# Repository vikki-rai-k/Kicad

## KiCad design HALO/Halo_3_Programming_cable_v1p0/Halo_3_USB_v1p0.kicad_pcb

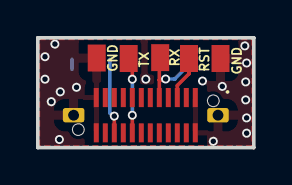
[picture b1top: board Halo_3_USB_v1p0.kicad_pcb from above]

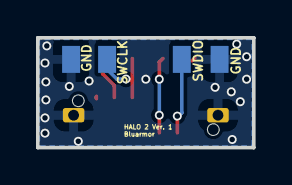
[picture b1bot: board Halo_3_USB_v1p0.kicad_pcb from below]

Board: 2 copper layers, 12.0 x 6.1 mm, 10 parts (4 on the bottom side), 5 nets.

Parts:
J1, J2, J3, J5, J6, J7, J8, J10, J11: Conn_01x01_Pin; Test_Point_1.5mm_SMD_Tiny
J4: Shouhan_TypeC_24_vertical

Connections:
/GND: J1.1, J2.1, J4.A1 (GND_1), J4.A12 (GND_2), J4.B1 (GND_3), J4.B12 (GND_4), J4.MH1, J4.MH2, J8.1, J11.1
/RTL_UART_RX: J3.1, J4.A5 (CC1), J6.1
/RTL_UART_TX: J4.B5 (CC2), J5.1
/ST_SWDIO: J4.B3 (SSTXN2), J7.1
/ST_nRST: J4.A3 (SSTXN1), J10.1

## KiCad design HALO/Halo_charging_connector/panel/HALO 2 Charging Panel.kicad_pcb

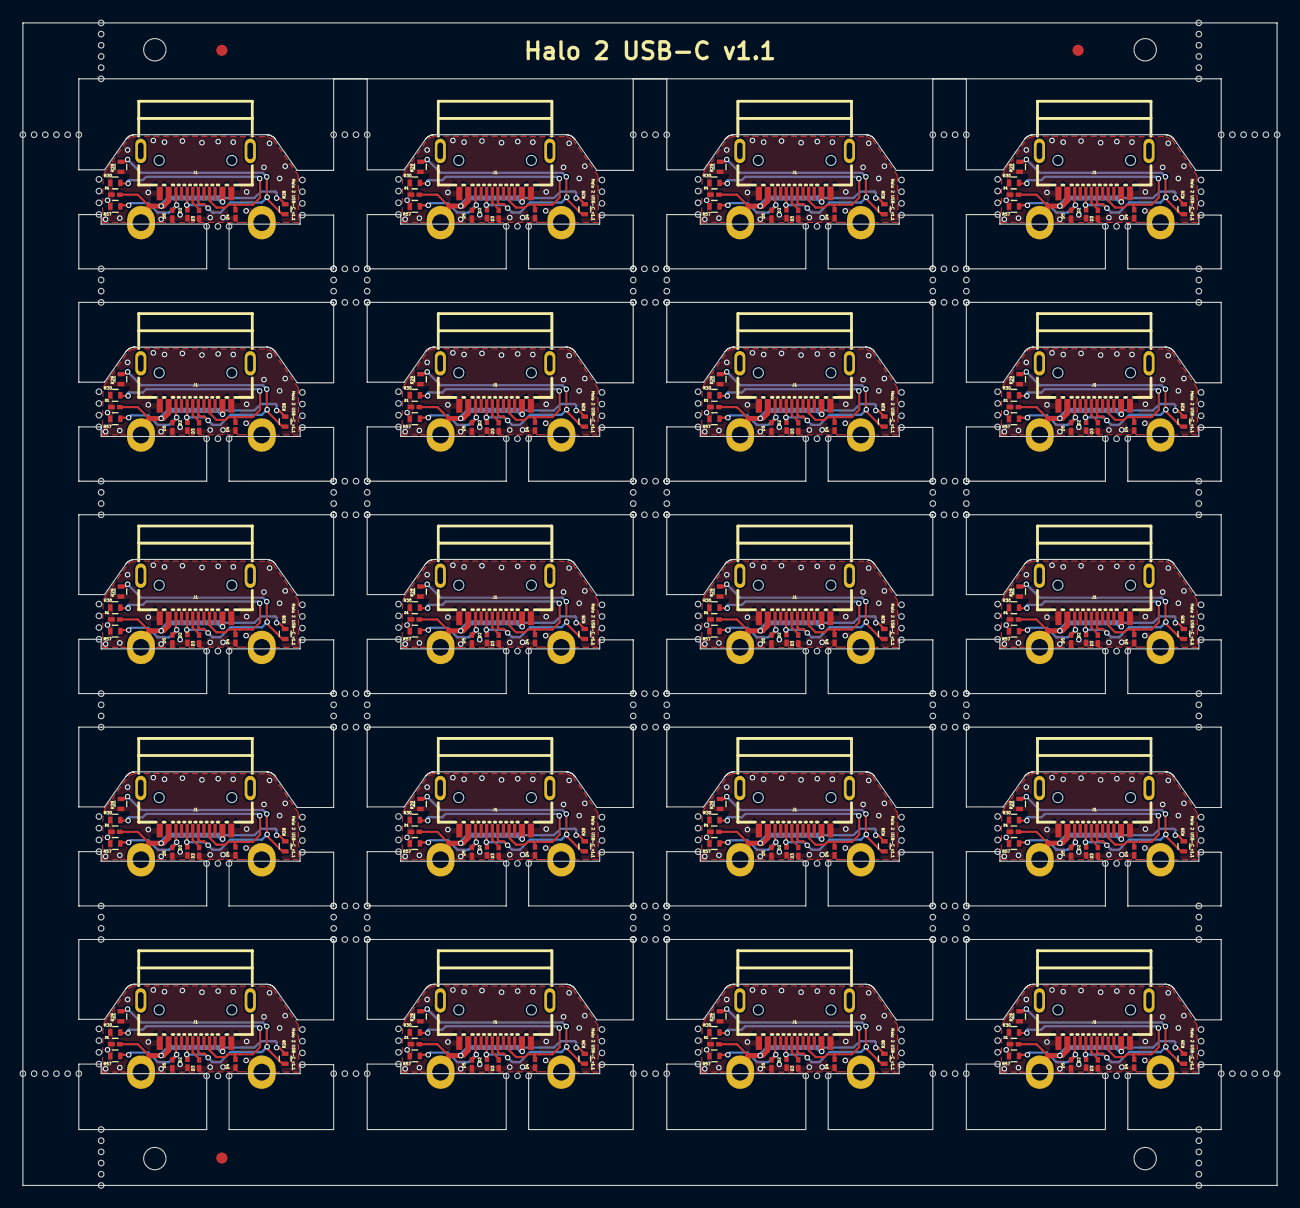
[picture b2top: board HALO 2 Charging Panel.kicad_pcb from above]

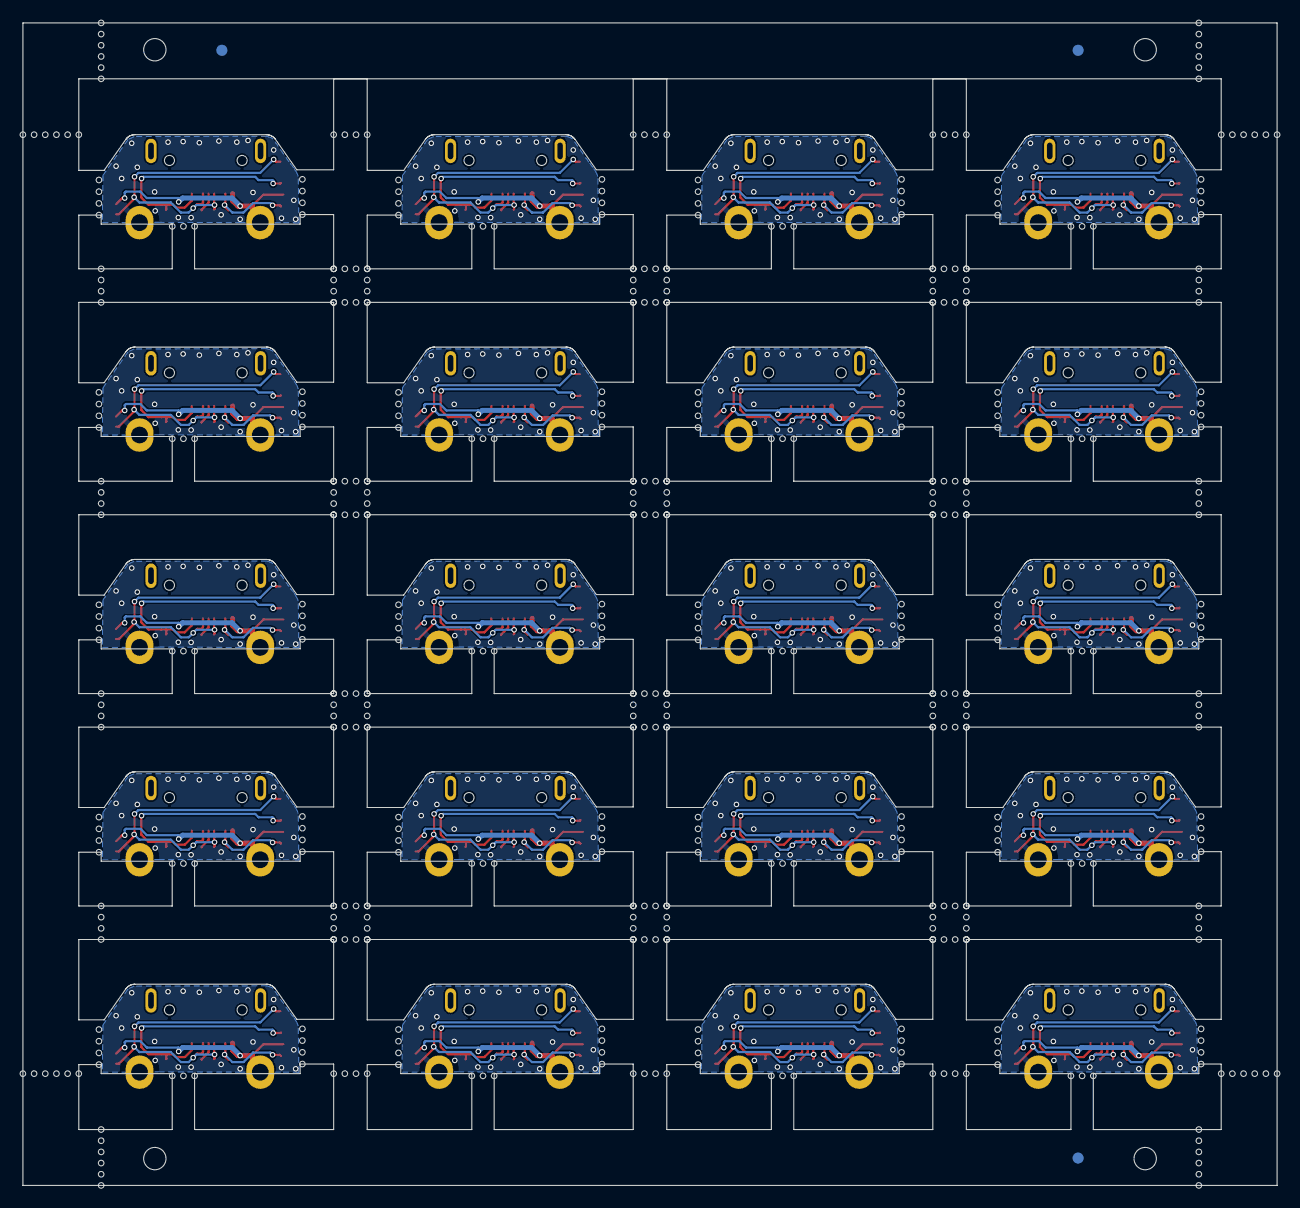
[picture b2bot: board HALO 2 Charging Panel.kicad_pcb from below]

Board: 2 copper layers, 112.2 x 104.0 mm, 766 parts (3 on the bottom side), 120 nets.

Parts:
D1, D1#2, D1#3, D1#4, D1#5, D1#6, D1#7, D1#8, D1#9, D1#10, D1#11, D1#12, D1#13, D1#14, D1#15, D1#16, D1#17, D1#18, D1#19, D1#20, D2, D2#2, D2#3, D2#4, D2#5, D2#6, D2#7, D2#8, D2#9, D2#10, D2#11, D2#12, D2#13, D2#14, D2#15, D2#16, D2#17, D2#18, D2#19, D2#20, D3, D3#2, D3#3, D3#4, D3#5, D3#6, D3#7, D3#8, D3#9, D3#10, D3#11, D3#12, D3#13, D3#14, D3#15, D3#16, D3#17, D3#18, D3#19, D3#20, D4, D4#2, D4#3, D4#4, D4#5, D4#6, D4#7, D4#8, D4#9, D4#10, D4#11, D4#12, D4#13, D4#14, D4#15, D4#16, D4#17, D4#18, D4#19, D4#20, D5, D5#2, D5#3, D5#4, D5#5, D5#6, D5#7, D5#8, D5#9, D5#10, D5#11, D5#12, D5#13, D5#14, D5#15, D5#16, D5#17, D5#18, D5#19, D5#20: ESD5451X2TR
J1, J1#2, J1#3, J1#4, J1#5, J1#6, J1#7, J1#8, J1#9, J1#10, J1#11, J1#12, J1#13, J1#14, J1#15, J1#16, J1#17, J1#18, J1#19, J1#20: TYPE-C 16PFS 2JCB1.6-H7.45 IPX8; USB-SMD_TYPE-C-16PFS-2J-H7.45-IPX8
KiKit_FID_B_1, KiKit_FID_B_2, KiKit_FID_B_3: Fiducial
KiKit_FID_T_1, KiKit_FID_T_2, KiKit_FID_T_3: Fiducial
KiKit_MB_1_1, KiKit_MB_1_2, KiKit_MB_1_3, KiKit_MB_2_1, KiKit_MB_2_2, KiKit_MB_2_3, KiKit_MB_2_4, KiKit_MB_3_2, KiKit_MB_3_3, KiKit_MB_3_4, KiKit_MB_3_5, KiKit_MB_4_1, KiKit_MB_4_2, KiKit_MB_4_3, KiKit_MB_5_1, KiKit_MB_5_2, KiKit_MB_5_3, KiKit_MB_5_4, KiKit_MB_6_2, KiKit_MB_6_3, KiKit_MB_6_4, KiKit_MB_6_5, KiKit_MB_7_1, KiKit_MB_7_2, KiKit_MB_7_3, KiKit_MB_8_1, KiKit_MB_8_2, KiKit_MB_8_3, KiKit_MB_8_4, KiKit_MB_9_2, KiKit_MB_9_3, KiKit_MB_9_4, KiKit_MB_9_5, KiKit_MB_10_1, KiKit_MB_10_2, KiKit_MB_10_3, KiKit_MB_11_1, KiKit_MB_11_2, KiKit_MB_11_3, KiKit_MB_11_4, KiKit_MB_12_2, KiKit_MB_12_3, KiKit_MB_12_4, KiKit_MB_12_5, KiKit_MB_13_1, KiKit_MB_13_2, KiKit_MB_13_3, KiKit_MB_14_1, KiKit_MB_14_2, KiKit_MB_14_3, KiKit_MB_14_4, KiKit_MB_15_2, KiKit_MB_15_3, KiKit_MB_15_4, KiKit_MB_15_5, KiKit_MB_16_1, KiKit_MB_16_2, KiKit_MB_16_3, KiKit_MB_17_1, KiKit_MB_17_2, KiKit_MB_17_3, KiKit_MB_17_4, KiKit_MB_18_2, KiKit_MB_18_3, KiKit_MB_18_4, KiKit_MB_18_5, KiKit_MB_19_1, KiKit_MB_19_2, KiKit_MB_19_3, KiKit_MB_20_1, KiKit_MB_20_2, KiKit_MB_20_3, KiKit_MB_20_4, KiKit_MB_21_2, KiKit_MB_21_3, KiKit_MB_21_4, KiKit_MB_21_5, KiKit_MB_22_1, KiKit_MB_22_2, KiKit_MB_22_3, KiKit_MB_23_1, KiKit_MB_23_2, KiKit_MB_23_3, KiKit_MB_23_4, KiKit_MB_24_2, KiKit_MB_24_3, KiKit_MB_24_4, KiKit_MB_24_5, KiKit_MB_25_1, KiKit_MB_25_2, KiKit_MB_25_3, KiKit_MB_26_1, KiKit_MB_26_2, KiKit_MB_26_3, KiKit_MB_26_4, KiKit_MB_27_2, KiKit_MB_27_3, KiKit_MB_27_4, KiKit_MB_27_5, KiKit_MB_28_1, KiKit_MB_28_2, KiKit_MB_28_3, KiKit_MB_29_1, KiKit_MB_29_2, KiKit_MB_29_3, KiKit_MB_29_4, KiKit_MB_30_2, KiKit_MB_30_3, KiKit_MB_30_4, KiKit_MB_30_5, KiKit_MB_31_1, KiKit_MB_31_2, KiKit_MB_31_3, KiKit_MB_32_1, KiKit_MB_32_2, KiKit_MB_32_3, KiKit_MB_32_4, KiKit_MB_33_2, KiKit_MB_33_3, KiKit_MB_33_4, KiKit_MB_33_5, KiKit_MB_34_1, KiKit_MB_34_2, KiKit_MB_34_3, KiKit_MB_35_1, KiKit_MB_35_2, KiKit_MB_35_3, KiKit_MB_35_4, KiKit_MB_36_2, KiKit_MB_36_3, KiKit_MB_36_4, KiKit_MB_36_5, KiKit_MB_37_1, KiKit_MB_37_2, KiKit_MB_37_3, KiKit_MB_38_1, KiKit_MB_38_2, KiKit_MB_38_3, KiKit_MB_38_4, KiKit_MB_39_2, KiKit_MB_39_3, KiKit_MB_39_4, KiKit_MB_39_5, KiKit_MB_40_1, KiKit_MB_40_2, KiKit_MB_40_3, KiKit_MB_41_1, KiKit_MB_41_2, KiKit_MB_41_3, KiKit_MB_41_4, KiKit_MB_42_2, KiKit_MB_42_3, KiKit_MB_42_4, KiKit_MB_42_5, KiKit_MB_43_1, KiKit_MB_43_2, KiKit_MB_43_3, KiKit_MB_44_1, KiKit_MB_44_2, KiKit_MB_44_3, KiKit_MB_44_4, KiKit_MB_45_2, KiKit_MB_45_3, KiKit_MB_45_4, KiKit_MB_45_5, KiKit_MB_46_1, KiKit_MB_46_2, KiKit_MB_46_3, KiKit_MB_47_1, KiKit_MB_47_2, KiKit_MB_47_3, KiKit_MB_47_4, KiKit_MB_48_2, KiKit_MB_48_3, KiKit_MB_48_4, KiKit_MB_48_5, KiKit_MB_49_1, KiKit_MB_49_2, KiKit_MB_49_3, KiKit_MB_50_1, KiKit_MB_50_2, KiKit_MB_50_3, KiKit_MB_50_4, KiKit_MB_51_2, KiKit_MB_51_3, KiKit_MB_51_4, KiKit_MB_51_5, KiKit_MB_52_1, KiKit_MB_52_2, KiKit_MB_52_3, KiKit_MB_53_1, KiKit_MB_53_2, KiKit_MB_53_3, KiKit_MB_53_4, KiKit_MB_54_2, KiKit_MB_54_3, KiKit_MB_54_4, KiKit_MB_54_5, KiKit_MB_55_1, KiKit_MB_55_2, KiKit_MB_55_3, KiKit_MB_56_1, KiKit_MB_56_2, KiKit_MB_56_3, KiKit_MB_56_4, KiKit_MB_57_2, KiKit_MB_57_3, KiKit_MB_57_4, KiKit_MB_57_5, KiKit_MB_58_1, KiKit_MB_58_2, KiKit_MB_58_3, KiKit_MB_59_1, KiKit_MB_59_2, KiKit_MB_59_3, KiKit_MB_59_4, KiKit_MB_60_2, KiKit_MB_60_3, KiKit_MB_60_4, KiKit_MB_60_5, KiKit_MB_61_1, KiKit_MB_61_2, KiKit_MB_61_3, KiKit_MB_61_4, KiKit_MB_62_1, KiKit_MB_62_2, KiKit_MB_62_3, KiKit_MB_62_4, KiKit_MB_63_1, KiKit_MB_63_2, KiKit_MB_63_3, KiKit_MB_63_4, KiKit_MB_64_1, KiKit_MB_64_2, KiKit_MB_64_3, KiKit_MB_64_4, KiKit_MB_65_1, KiKit_MB_65_2, KiKit_MB_65_3, KiKit_MB_65_4, KiKit_MB_66_1, KiKit_MB_66_2, KiKit_MB_66_3, KiKit_MB_66_4, KiKit_MB_67_1, KiKit_MB_67_2, KiKit_MB_67_3, KiKit_MB_67_4, KiKit_MB_68_1, KiKit_MB_68_2, KiKit_MB_68_3, KiKit_MB_68_4, KiKit_MB_69_1, KiKit_MB_69_2, KiKit_MB_69_3, KiKit_MB_69_4, KiKit_MB_70_1, KiKit_MB_70_2, KiKit_MB_70_3, KiKit_MB_70_4, KiKit_MB_71_1, KiKit_MB_71_2, KiKit_MB_71_3, KiKit_MB_71_4, KiKit_MB_72_1, KiKit_MB_72_2, KiKit_MB_72_3, KiKit_MB_72_4, KiKit_MB_73_1, KiKit_MB_73_2, KiKit_MB_73_3, KiKit_MB_73_4, KiKit_MB_74_1, KiKit_MB_74_2, KiKit_MB_74_3, KiKit_MB_74_4, KiKit_MB_75_1, KiKit_MB_75_2, KiKit_MB_75_3, KiKit_MB_75_4, KiKit_MB_76_1, KiKit_MB_76_2, KiKit_MB_76_3, KiKit_MB_76_4, KiKit_MB_77_1, KiKit_MB_77_2, KiKit_MB_77_3, KiKit_MB_77_4, KiKit_MB_78_1, KiKit_MB_78_2, KiKit_MB_78_3, KiKit_MB_78_4, KiKit_MB_79_1, KiKit_MB_79_2, KiKit_MB_79_3, KiKit_MB_79_4, KiKit_MB_80_1, KiKit_MB_80_2, KiKit_MB_80_3, KiKit_MB_80_4, KiKit_MB_81_1, KiKit_MB_81_2, KiKit_MB_81_3, KiKit_MB_81_4, KiKit_MB_82_1, KiKit_MB_82_2, KiKit_MB_82_3, KiKit_MB_82_4, KiKit_MB_83_1, KiKit_MB_83_2, KiKit_MB_83_3, KiKit_MB_83_4, KiKit_MB_84_1, KiKit_MB_84_2, KiKit_MB_84_3, KiKit_MB_84_4, KiKit_MB_85_1, KiKit_MB_85_2, KiKit_MB_85_3, KiKit_MB_85_4, KiKit_MB_86_1, KiKit_MB_86_2, KiKit_MB_86_3, KiKit_MB_86_4, KiKit_MB_87_1, KiKit_MB_87_2, KiKit_MB_87_3, KiKit_MB_87_4, KiKit_MB_88_1, KiKit_MB_88_2, KiKit_MB_88_3, KiKit_MB_88_4, KiKit_MB_89_1, KiKit_MB_89_2, KiKit_MB_89_3, KiKit_MB_89_4, KiKit_MB_90_1, KiKit_MB_90_2, KiKit_MB_90_3, KiKit_MB_90_4, KiKit_MB_91_1, KiKit_MB_91_2, KiKit_MB_91_3, KiKit_MB_91_4, KiKit_MB_92_1, KiKit_MB_92_2, KiKit_MB_92_3, KiKit_MB_92_4, KiKit_MB_93_1, KiKit_MB_93_2, KiKit_MB_93_3, KiKit_MB_93_4, KiKit_MB_94_1, KiKit_MB_94_2, KiKit_MB_94_3, KiKit_MB_94_4, KiKit_MB_95_1, KiKit_MB_95_2, KiKit_MB_95_3, KiKit_MB_95_4, KiKit_MB_96_1, KiKit_MB_96_2, KiKit_MB_96_3, KiKit_MB_96_4, KiKit_MB_97_1, KiKit_MB_97_2, KiKit_MB_97_3, KiKit_MB_97_4, KiKit_MB_98_1, KiKit_MB_98_2, KiKit_MB_98_3, KiKit_MB_98_4, KiKit_MB_99_1, KiKit_MB_99_2, KiKit_MB_99_3, KiKit_MB_99_4, KiKit_MB_100_1, KiKit_MB_100_2, KiKit_MB_100_3, KiKit_MB_100_4, KiKit_MB_101_1, KiKit_MB_101_2, KiKit_MB_101_3, KiKit_MB_101_4, KiKit_MB_102_1, KiKit_MB_102_2, KiKit_MB_102_3, KiKit_MB_102_4, KiKit_MB_103_1, KiKit_MB_103_2, KiKit_MB_103_3, KiKit_MB_103_4, KiKit_MB_104_1, KiKit_MB_104_2, KiKit_MB_104_3, KiKit_MB_104_4, KiKit_MB_105_1, KiKit_MB_105_2, KiKit_MB_105_3, KiKit_MB_105_4, KiKit_MB_106_1, KiKit_MB_106_2, KiKit_MB_106_3, KiKit_MB_106_4, KiKit_MB_107_1, KiKit_MB_107_2, KiKit_MB_107_3, KiKit_MB_107_4, KiKit_MB_108_1, KiKit_MB_108_2, KiKit_MB_108_3, KiKit_MB_108_4, KiKit_MB_109_1, KiKit_MB_109_2, KiKit_MB_109_3, KiKit_MB_109_4, KiKit_MB_110_1, KiKit_MB_110_2, KiKit_MB_110_3, KiKit_MB_110_4, KiKit_MB_111_1, KiKit_MB_111_2, KiKit_MB_111_3, KiKit_MB_111_4, KiKit_MB_112_1, KiKit_MB_112_2, KiKit_MB_112_3, KiKit_MB_112_4, KiKit_MB_113_1, KiKit_MB_113_2, KiKit_MB_113_3, KiKit_MB_113_4, KiKit_MB_114_1, KiKit_MB_114_2, KiKit_MB_114_3, KiKit_MB_114_4, KiKit_MB_115_1, KiKit_MB_115_2, KiKit_MB_115_3, KiKit_MB_115_4, KiKit_MB_116_1, KiKit_MB_116_2, KiKit_MB_116_3, KiKit_MB_116_4, KiKit_MB_117_1, KiKit_MB_117_2, KiKit_MB_117_3, KiKit_MB_117_4, KiKit_MB_118_1, KiKit_MB_118_2, KiKit_MB_118_3, KiKit_MB_118_4, KiKit_MB_119_1, KiKit_MB_119_2, KiKit_MB_119_3, KiKit_MB_119_4, KiKit_MB_120_1, KiKit_MB_120_2, KiKit_MB_120_3, KiKit_MB_120_4, KiKit_MB_121_1, KiKit_MB_121_2, KiKit_MB_121_3, KiKit_MB_121_4, KiKit_MB_122_1, KiKit_MB_122_2, KiKit_MB_122_3, KiKit_MB_122_4, KiKit_MB_123_1, KiKit_MB_123_2, KiKit_MB_123_3, KiKit_MB_123_4, KiKit_MB_123_5, KiKit_MB_123_6, KiKit_MB_124_1, KiKit_MB_124_2, KiKit_MB_124_3, KiKit_MB_124_4, KiKit_MB_124_5, KiKit_MB_124_6, KiKit_MB_125_1, KiKit_MB_125_2, KiKit_MB_125_3, KiKit_MB_125_4, KiKit_MB_125_5, KiKit_MB_125_6, KiKit_MB_126_1, KiKit_MB_126_2, KiKit_MB_126_3, KiKit_MB_126_4, KiKit_MB_126_5, KiKit_MB_126_6, KiKit_MB_127_1, KiKit_MB_127_2, KiKit_MB_127_3, KiKit_MB_127_4, KiKit_MB_127_5, KiKit_MB_127_6, KiKit_MB_128_1, KiKit_MB_128_2, KiKit_MB_128_3, KiKit_MB_128_4, KiKit_MB_128_5, KiKit_MB_128_6, KiKit_MB_129_1, KiKit_MB_129_2, KiKit_MB_129_3, KiKit_MB_129_4, KiKit_MB_129_5, KiKit_MB_129_6, KiKit_MB_130_1, KiKit_MB_130_2, KiKit_MB_130_3, KiKit_MB_130_4, KiKit_MB_130_5, KiKit_MB_130_6: NPTH
KiKit_TO_1, KiKit_TO_2, KiKit_TO_3, KiKit_TO_4: NPTH
R28, R28#2, R28#3, R28#4, R28#5, R28#6, R28#7, R28#8, R28#9, R28#10, R28#11, R28#12, R28#13, R28#14, R28#15, R28#16, R28#17, R28#18, R28#19, R28#20: 60.4K; R_0402
R29, R29#2, R29#3, R29#4, R29#5, R29#6, R29#7, R29#8, R29#9, R29#10, R29#11, R29#12, R29#13, R29#14, R29#15, R29#16, R29#17, R29#18, R29#19, R29#20: 10K; R_0402
R30, R30#2, R30#3, R30#4, R30#5, R30#6, R30#7, R30#8, R30#9, R30#10, R30#11, R30#12, R30#13, R30#14, R30#15, R30#16, R30#17, R30#18, R30#19, R30#20, R57, R57#2, R57#3, R57#4, R57#5, R57#6, R57#7, R57#8, R57#9, R57#10, R57#11, R57#12, R57#13, R57#14, R57#15, R57#16, R57#17, R57#18, R57#19, R57#20: 5.1K; R_0402
U1, U1#2, U1#3, U1#4, U1#5, U1#6, U1#7, U1#8, U1#9, U1#10, U1#11, U1#12, U1#13, U1#14, U1#15, U1#16, U1#17, U1#18, U1#19, U1#20, U2, U2#2, U2#3, U2#4, U2#5, U2#6, U2#7, U2#8, U2#9, U2#10, U2#11, U2#12, U2#13, U2#14, U2#15, U2#16, U2#17, U2#18, U2#19, U2#20: -; Halo_2_USBC_Charging_PCB_Castellated_holes

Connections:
Board_0-/CC1: D4#6.2 (A2), J1#15.A5 (CC1), R30#20.1
Board_0-/CC2: D5#17.2 (A2), J1#15.B5 (CC2), R57#17.1
Board_0-/DN: D3#16.2 (A2), J1#15.A7 (DA_N)
Board_0-/DP: D2#15.2 (A2), J1#15.A6 (DA_P), J1#15.B6 (DB_P), R28#20.2, R29#2.1
Board_0-/GND: D1#12.1 (A1), D2#15.1 (A1), D3#16.1 (A1), D4#6.1 (A1), D5#17.1 (A1), J1#15.B1A12 (GNDB), J1#15.B12A1 (GNDA), R29#2.2, R30#20.2, R57#17.2, U2#20.1
Board_0-/VUSB: D1#12.2 (A2), J1#15.A4B9 (VBUS_A), J1#15.A9B4 (VBUS_B), R28#20.1, U1#11.1
Board_1-/CC1: D4#20.2 (A2), J1#4.A5 (CC1), R30#15.1
Board_1-/CC2: D5#3.2 (A2), J1#4.B5 (CC2), R57#11.1
Board_1-/DN: D3#6.2 (A2), J1#4.A7 (DA_N)
Board_1-/DP: D2#12.2 (A2), J1#4.A6 (DA_P), J1#4.B6 (DB_P), R28#19.2, R29#7.1
Board_1-/GND: D1#9.1 (A1), D2#12.1 (A1), D3#6.1 (A1), D4#20.1 (A1), D5#3.1 (A1), J1#4.B1A12 (GNDB), J1#4.B12A1 (GNDA), R29#7.2, R30#15.2, R57#11.2, U2#4.1
Board_1-/VUSB: D1#9.2 (A2), J1#4.A4B9 (VBUS_A), J1#4.A9B4 (VBUS_B), R28#19.1, U1#13.1
Board_2-/CC1: D4#5.2 (A2), J1#3.A5 (CC1), R30#10.1
Board_2-/CC2: D5#11.2 (A2), J1#3.B5 (CC2), R57#13.1
Board_2-/DN: D3#2.2 (A2), J1#3.A7 (DA_N)
Board_2-/DP: D2#20.2 (A2), J1#3.A6 (DA_P), J1#3.B6 (DB_P), R28#17.2, R29#8.1
Board_2-/GND: D1#11.1 (A1), D2#20.1 (A1), D3#2.1 (A1), D4#5.1 (A1), D5#11.1 (A1), J1#3.B1A12 (GNDB), J1#3.B12A1 (GNDA), R29#8.2, R30#10.2, R57#13.2, U2#17.1
Board_2-/VUSB: D1#11.2 (A2), J1#3.A4B9 (VBUS_A), J1#3.A9B4 (VBUS_B), R28#17.1, U1#5.1
Board_3-/CC1: D4#16.2 (A2), J1#16.A5 (CC1), R30#14.1
Board_3-/CC2: D5#18.2 (A2), J1#16.B5 (CC2), R57#5.1
Board_3-/DN: D3#5.2 (A2), J1#16.A7 (DA_N)
Board_3-/DP: D2#14.2 (A2), J1#16.A6 (DA_P), J1#16.B6 (DB_P), R28#16.2, R29#19.1
Board_3-/GND: D1#5.1 (A1), D2#14.1 (A1), D3#5.1 (A1), D4#16.1 (A1), D5#18.1 (A1), J1#16.B1A12 (GNDB), J1#16.B12A1 (GNDA), R29#19.2, R30#14.2, R57#5.2, U2#10.1
Board_3-/VUSB: D1#5.2 (A2), J1#16.A4B9 (VBUS_A), J1#16.A9B4 (VBUS_B), R28#16.1, U1#6.1
Board_4-/CC1: D4#11.2 (A2), J1#19.A5 (CC1), R30#2.1
Board_4-/CC2: D5#15.2 (A2), J1#19.B5 (CC2), R57#18.1
Board_4-/DN: D3#20.2 (A2), J1#19.A7 (DA_N)
Board_4-/DP: D2#5.2 (A2), J1#19.A6 (DA_P), J1#19.B6 (DB_P), R28#4.2, R29#11.1
Board_4-/GND: D1#2.1 (A1), D2#5.1 (A1), D3#20.1 (A1), D4#11.1 (A1), D5#15.1 (A1), J1#19.B1A12 (GNDB), J1#19.B12A1 (GNDA), R29#11.2, R30#2.2, R57#18.2, U2#19.1
Board_4-/VUSB: D1#2.2 (A2), J1#19.A4B9 (VBUS_A), J1#19.A9B4 (VBUS_B), R28#4.1, U1#8.1
Board_5-/CC1: D4#15.2 (A2), J1#2.A5 (CC1), R30#16.1
Board_5-/CC2: D5#14.2 (A2), J1#2.B5 (CC2), R57#8.1
Board_5-/DN: D3#8.2 (A2), J1#2.A7 (DA_N)
Board_5-/DP: D2#18.2 (A2), J1#2.A6 (DA_P), J1#2.B6 (DB_P), R28#10.2, R29#3.1
Board_5-/GND: D1#16.1 (A1), D2#18.1 (A1), D3#8.1 (A1), D4#15.1 (A1), D5#14.1 (A1), J1#2.B1A12 (GNDB), J1#2.B12A1 (GNDA), R29#3.2, R30#16.2, R57#8.2, U2#14.1
Board_5-/VUSB: D1#16.2 (A2), J1#2.A4B9 (VBUS_A), J1#2.A9B4 (VBUS_B), R28#10.1, U1#18.1
Board_6-/CC1: D4#9.2 (A2), J1#9.A5 (CC1), R30#19.1
Board_6-/CC2: D5#19.2 (A2), J1#9.B5 (CC2), R57#10.1
Board_6-/DN: D3#10.2 (A2), J1#9.A7 (DA_N)
Board_6-/DP: D2#11.2 (A2), J1#9.A6 (DA_P), J1#9.B6 (DB_P), R28#6.2, R29#15.1
Board_6-/GND: D1#20.1 (A1), D2#11.1 (A1), D3#10.1 (A1), D4#9.1 (A1), D5#19.1 (A1), J1#9.B1A12 (GNDB), J1#9.B12A1 (GNDA), R29#15.2, R30#19.2, R57#10.2, U2#8.1
Board_6-/VUSB: D1#20.2 (A2), J1#9.A4B9 (VBUS_A), J1#9.A9B4 (VBUS_B), R28#6.1, U1#4.1
Board_7-/CC1: D4#2.2 (A2), J1.A5 (CC1), R30#3.1
Board_7-/CC2: D5#5.2 (A2), J1.B5 (CC2), R57#19.1
Board_7-/DN: D3#11.2 (A2), J1.A7 (DA_N)
Board_7-/DP: D2#4.2 (A2), J1.A6 (DA_P), J1.B6 (DB_P), R28#11.2, R29#20.1
Board_7-/GND: D1#19.1 (A1), D2#4.1 (A1), D3#11.1 (A1), D4#2.1 (A1), D5#5.1 (A1), J1.B1A12 (GNDB), J1.B12A1 (GNDA), R29#20.2, R30#3.2, R57#19.2, U2#16.1
Board_7-/VUSB: D1#19.2 (A2), J1.A4B9 (VBUS_A), J1.A9B4 (VBUS_B), R28#11.1, U1#19.1
Board_8-/CC1: D4#12.2 (A2), J1#20.A5 (CC1), R30#4.1
Board_8-/CC2: D5#7.2 (A2), J1#20.B5 (CC2), R57#20.1
Board_8-/DN: D3#12.2 (A2), J1#20.A7 (DA_N)
Board_8-/DP: D2.2 (A2), J1#20.A6 (DA_P), J1#20.B6 (DB_P), R28#9.2, R29#12.1
Board_8-/GND: D1.1 (A1), D2.1 (A1), D3#12.1 (A1), D4#12.1 (A1), D5#7.1 (A1), J1#20.B1A12 (GNDB), J1#20.B12A1 (GNDA), R29#12.2, R30#4.2, R57#20.2, U2#6.1
Board_8-/VUSB: D1.2 (A2), J1#20.A4B9 (VBUS_A), J1#20.A9B4 (VBUS_B), R28#9.1, U1#16.1
Board_9-/CC1: D4#4.2 (A2), J1#8.A5 (CC1), R30#17.1
Board_9-/CC2: D5#20.2 (A2), J1#8.B5 (CC2), R57#6.1
Board_9-/DN: D3#19.2 (A2), J1#8.A7 (DA_N)
Board_9-/DP: D2#7.2 (A2), J1#8.A6 (DA_P), J1#8.B6 (DB_P), R28#14.2, R29#16.1
Board_9-/GND: D1#8.1 (A1), D2#7.1 (A1), D3#19.1 (A1), D4#4.1 (A1), D5#20.1 (A1), J1#8.B1A12 (GNDB), J1#8.B12A1 (GNDA), R29#16.2, R30#17.2, R57#6.2, U2.1
Board_9-/VUSB: D1#8.2 (A2), J1#8.A4B9 (VBUS_A), J1#8.A9B4 (VBUS_B), R28#14.1, U1#7.1
Board_10-/CC1: D4#13.2 (A2), J1#10.A5 (CC1), R30#6.1
Board_10-/CC2: D5.2 (A2), J1#10.B5 (CC2), R57#7.1
Board_10-/DN: D3#13.2 (A2), J1#10.A7 (DA_N)
Board_10-/DP: D2#6.2 (A2), J1#10.A6 (DA_P), J1#10.B6 (DB_P), R28#13.2, R29#6.1
Board_10-/GND: D1#17.1 (A1), D2#6.1 (A1), D3#13.1 (A1), D4#13.1 (A1), D5.1 (A1), J1#10.B1A12 (GNDB), J1#10.B12A1 (GNDA), R29#6.2, R30#6.2, R57#7.2, U2#11.1
Board_10-/VUSB: D1#17.2 (A2), J1#10.A4B9 (VBUS_A), J1#10.A9B4 (VBUS_B), R28#13.1, U1#20.1
Board_11-/CC1: D4#14.2 (A2), J1#13.A5 (CC1), R30#9.1
Board_11-/CC2: D5#6.2 (A2), J1#13.B5 (CC2), R57#3.1
Board_11-/DN: D3#14.2 (A2), J1#13.A7 (DA_N)
Board_11-/DP: D2#17.2 (A2), J1#13.A6 (DA_P), J1#13.B6 (DB_P), R28#7.2, R29.1
Board_11-/GND: D1#6.1 (A1), D2#17.1 (A1), D3#14.1 (A1), D4#14.1 (A1), D5#6.1 (A1), J1#13.B1A12 (GNDB), J1#13.B12A1 (GNDA), R29.2, R30#9.2, R57#3.2, U2#3.1
Board_11-/VUSB: D1#6.2 (A2), J1#13.A4B9 (VBUS_A), J1#13.A9B4 (VBUS_B), R28#7.1, U1#10.1
Board_12-/CC1: D4#8.2 (A2), J1#7.A5 (CC1), R30#12.1
Board_12-/CC2: D5#13.2 (A2), J1#7.B5 (CC2), R57#4.1
Board_12-/DN: D3.2 (A2), J1#7.A7 (DA_N)
Board_12-/DP: D2#2.2 (A2), J1#7.A6 (DA_P), J1#7.B6 (DB_P), R28#3.2, R29#18.1
Board_12-/GND: D1#13.1 (A1), D2#2.1 (A1), D3.1 (A1), D4#8.1 (A1), D5#13.1 (A1), J1#7.B1A12 (GNDB), J1#7.B12A1 (GNDA), R29#18.2, R30#12.2, R57#4.2, U2#18.1
Board_12-/VUSB: D1#13.2 (A2), J1#7.A4B9 (VBUS_A), J1#7.A9B4 (VBUS_B), R28#3.1, U1#15.1
Board_13-/CC1: D4#10.2 (A2), J1#14.A5 (CC1), R30#8.1
Board_13-/CC2: D5#8.2 (A2), J1#14.B5 (CC2), R57#15.1
Board_13-/DN: D3#4.2 (A2), J1#14.A7 (DA_N)
Board_13-/DP: D2#13.2 (A2), J1#14.A6 (DA_P), J1#14.B6 (DB_P), R28#12.2, R29#17.1
Board_13-/GND: D1#3.1 (A1), D2#13.1 (A1), D3#4.1 (A1), D4#10.1 (A1), D5#8.1 (A1), J1#14.B1A12 (GNDB), J1#14.B12A1 (GNDA), R29#17.2, R30#8.2, R57#15.2, U2#2.1
Board_13-/VUSB: D1#3.2 (A2), J1#14.A4B9 (VBUS_A), J1#14.A9B4 (VBUS_B), R28#12.1, U1#9.1
Board_14-/CC1: D4#19.2 (A2), J1#11.A5 (CC1), R30#18.1
Board_14-/CC2: D5#4.2 (A2), J1#11.B5 (CC2), R57#12.1
Board_14-/DN: D3#7.2 (A2), J1#11.A7 (DA_N)
Board_14-/DP: D2#19.2 (A2), J1#11.A6 (DA_P), J1#11.B6 (DB_P), R28.2, R29#4.1
Board_14-/GND: D1#4.1 (A1), D2#19.1 (A1), D3#7.1 (A1), D4#19.1 (A1), D5#4.1 (A1), J1#11.B1A12 (GNDB), J1#11.B12A1 (GNDA), R29#4.2, R30#18.2, R57#12.2, U2#7.1
Board_14-/VUSB: D1#4.2 (A2), J1#11.A4B9 (VBUS_A), J1#11.A9B4 (VBUS_B), R28.1, U1#2.1
Board_15-/CC1: D4#7.2 (A2), J1#12.A5 (CC1), R30.1
Board_15-/CC2: D5#12.2 (A2), J1#12.B5 (CC2), R57#9.1
Board_15-/DN: D3#9.2 (A2), J1#12.A7 (DA_N)
Board_15-/DP: D2#9.2 (A2), J1#12.A6 (DA_P), J1#12.B6 (DB_P), R28#5.2, R29#5.1
Board_15-/GND: D1#15.1 (A1), D2#9.1 (A1), D3#9.1 (A1), D4#7.1 (A1), D5#12.1 (A1), J1#12.B1A12 (GNDB), J1#12.B12A1 (GNDA), R29#5.2, R30.2, R57#9.2, U2#13.1
Board_15-/VUSB: D1#15.2 (A2), J1#12.A4B9 (VBUS_A), J1#12.A9B4 (VBUS_B), R28#5.1, U1#12.1
Board_16-/CC1: D4#18.2 (A2), J1#17.A5 (CC1), R30#5.1
Board_16-/CC2: D5#2.2 (A2), J1#17.B5 (CC2), R57.1
Board_16-/DN: D3#3.2 (A2), J1#17.A7 (DA_N)
Board_16-/DP: D2#16.2 (A2), J1#17.A6 (DA_P), J1#17.B6 (DB_P), R28#15.2, R29#14.1
Board_16-/GND: D1#14.1 (A1), D2#16.1 (A1), D3#3.1 (A1), D4#18.1 (A1), D5#2.1 (A1), J1#17.B1A12 (GNDB), J1#17.B12A1 (GNDA), R29#14.2, R30#5.2, R57.2, U2#5.1
Board_16-/VUSB: D1#14.2 (A2), J1#17.A4B9 (VBUS_A), J1#17.A9B4 (VBUS_B), R28#15.1, U1#17.1
Board_17-/CC1: D4#17.2 (A2), J1#5.A5 (CC1), R30#11.1
Board_17-/CC2: D5#16.2 (A2), J1#5.B5 (CC2), R57#2.1
Board_17-/DN: D3#18.2 (A2), J1#5.A7 (DA_N)
Board_17-/DP: D2#3.2 (A2), J1#5.A6 (DA_P), J1#5.B6 (DB_P), R28#18.2, R29#10.1
Board_17-/GND: D1#7.1 (A1), D2#3.1 (A1), D3#18.1 (A1), D4#17.1 (A1), D5#16.1 (A1), J1#5.B1A12 (GNDB), J1#5.B12A1 (GNDA), R29#10.2, R30#11.2, R57#2.2, U2#15.1
Board_17-/VUSB: D1#7.2 (A2), J1#5.A4B9 (VBUS_A), J1#5.A9B4 (VBUS_B), R28#18.1, U1#14.1
Board_18-/CC1: D4#3.2 (A2), J1#18.A5 (CC1), R30#13.1
Board_18-/CC2: D5#10.2 (A2), J1#18.B5 (CC2), R57#14.1
Board_18-/DN: D3#17.2 (A2), J1#18.A7 (DA_N)
Board_18-/DP: D2#10.2 (A2), J1#18.A6 (DA_P), J1#18.B6 (DB_P), R28#2.2, R29#13.1
Board_18-/GND: D1#10.1 (A1), D2#10.1 (A1), D3#17.1 (A1), D4#3.1 (A1), D5#10.1 (A1), J1#18.B1A12 (GNDB), J1#18.B12A1 (GNDA), R29#13.2, R30#13.2, R57#14.2, U2#12.1
Board_18-/VUSB: D1#10.2 (A2), J1#18.A4B9 (VBUS_A), J1#18.A9B4 (VBUS_B), R28#2.1, U1#3.1
Board_19-/CC1: D4.2 (A2), J1#6.A5 (CC1), R30#7.1
Board_19-/CC2: D5#9.2 (A2), J1#6.B5 (CC2), R57#16.1
Board_19-/DN: D3#15.2 (A2), J1#6.A7 (DA_N)
Board_19-/DP: D2#8.2 (A2), J1#6.A6 (DA_P), J1#6.B6 (DB_P), R28#8.2, R29#9.1
Board_19-/GND: D1#18.1 (A1), D2#8.1 (A1), D3#15.1 (A1), D4.1 (A1), D5#9.1 (A1), J1#6.B1A12 (GNDB), J1#6.B12A1 (GNDA), R29#9.2, R30#7.2, R57#16.2, U2#9.1
Board_19-/VUSB: D1#18.2 (A2), J1#6.A4B9 (VBUS_A), J1#6.A9B4 (VBUS_B), R28#8.1, U1.1

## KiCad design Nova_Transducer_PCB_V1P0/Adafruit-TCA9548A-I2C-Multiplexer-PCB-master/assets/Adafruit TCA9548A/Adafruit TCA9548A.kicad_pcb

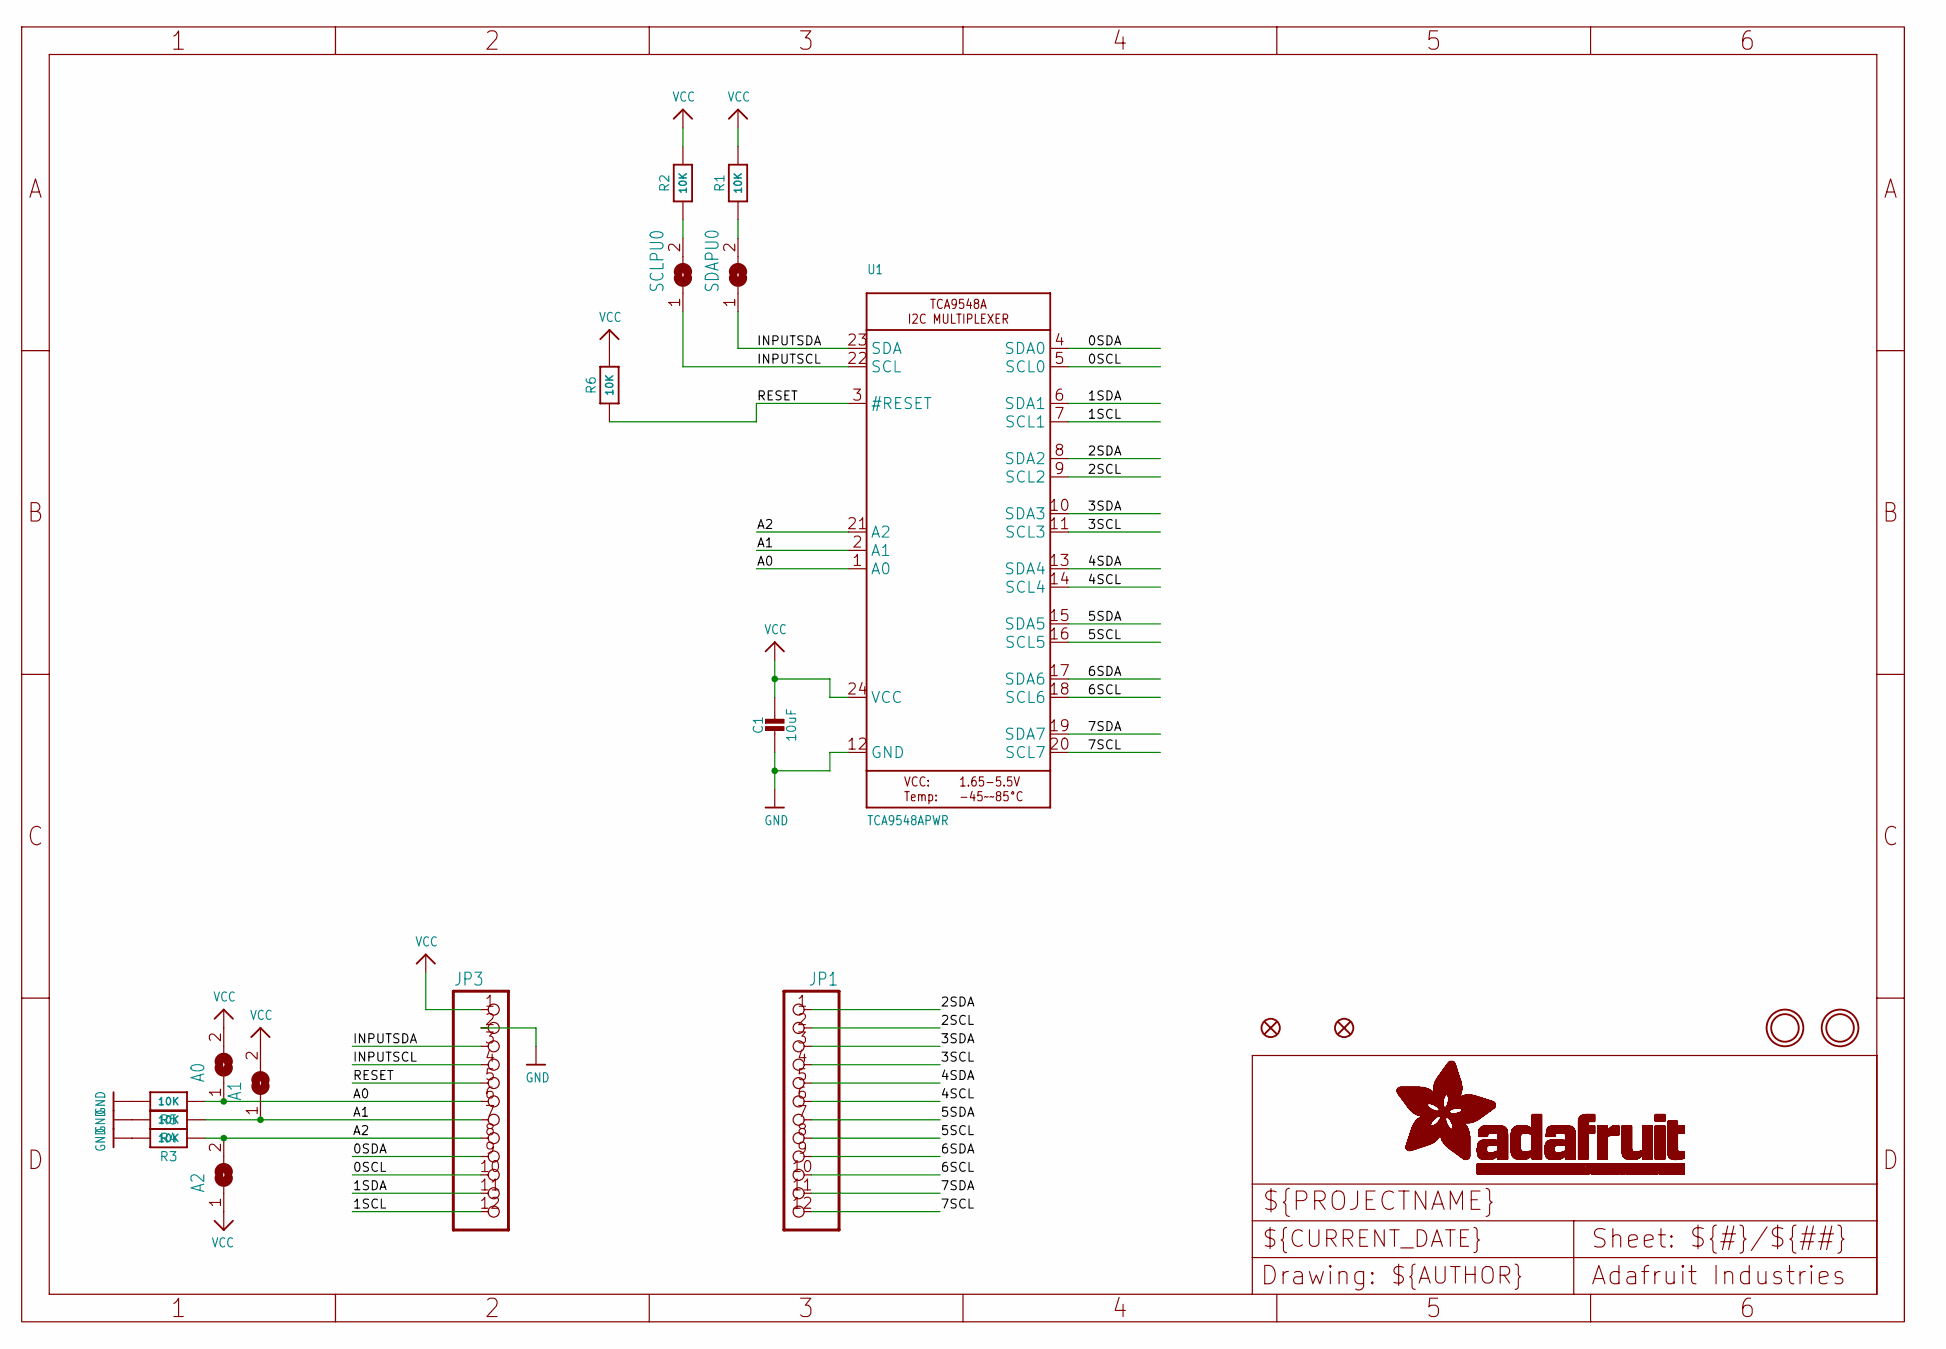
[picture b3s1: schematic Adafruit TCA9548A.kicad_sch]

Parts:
A0, A1, A2: SOLDERJUMPER; SOLDERJUMPER_ARROW_NOPASTE
C1: 10uF; 0805-NO
FID1, FID3: FIDUCIAL""; FIDUCIAL_1MM
JP1, JP3: HEADER-1X12; 1X12_ROUND
R1, R2, R3, R4, R5: 10K; 0805-NO
R6: 10K; _0805MP
SCLPU0: SOLDERJUMPERCLOSED; SOLDERJUMPER_CLOSEDWIRE
SDAPU0: SOLDERJUMPERCLOSED; SOLDERJUMPER_CLOSEDWIRE
U1: TCA9548APWR; TSSOP24
U$4, U$5: MOUNTINGHOLE2.5; MOUNTINGHOLE_2.5_PLATED

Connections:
0SCL: JP3.10, U1.5 (SCL0)
0SDA: JP3.9, U1.4 (SDA0)
1SCL: JP3.12, U1.7 (SCL1)
1SDA: JP3.11, U1.6 (SDA1)
2SCL: JP1.2, U1.9 (SCL2)
2SDA: JP1.1, U1.8 (SDA2)
3SCL: JP1.4, U1.11 (SCL3)
3SDA: JP1.3, U1.10 (SDA3)
4SCL: JP1.6, U1.14 (SCL4)
4SDA: JP1.5, U1.13 (SDA4)
5SCL: JP1.8, U1.16 (SCL5)
5SDA: JP1.7, U1.15 (SDA5)
6SCL: JP1.10, U1.18 (SCL6)
6SDA: JP1.9, U1.17 (SDA6)
7SCL: JP1.12, U1.20 (SCL7)
7SDA: JP1.11, U1.19 (SDA7)
A0: A0.1, JP3.6, R5.1, U1.1 (A0)
A1: A1.1, JP3.7, R4.1, U1.2 (A1)
A2: A2.2, JP3.8, R3.1, U1.21 (A2)
GND: C1.2, JP3.2, R3.2, R4.2, R5.2, U1.12 (GND)
INPUTSCL: JP3.4, SCLPU0.1, U1.22 (SCL)
INPUTSDA: JP3.3, SDAPU0.1, U1.23 (SDA)
unnamed: R2.1, SCLPU0.2
unnamed: R1.1, SDAPU0.2
RESET: JP3.5, R6.1, U1.3 (#RESET)
VCC: A0.2, A1.2, A2.1, C1.1, JP3.1, R1.2, R2.2, R6.2, U1.24 (VCC)

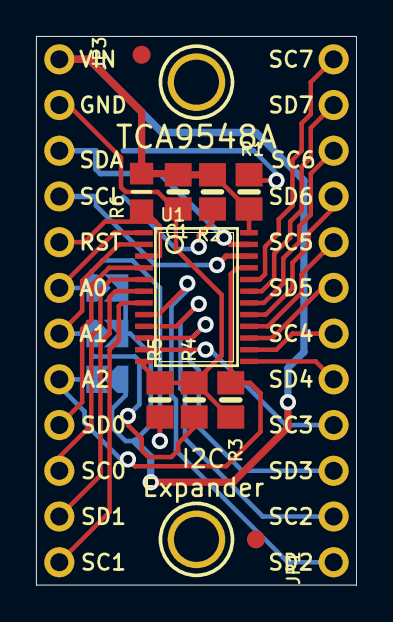
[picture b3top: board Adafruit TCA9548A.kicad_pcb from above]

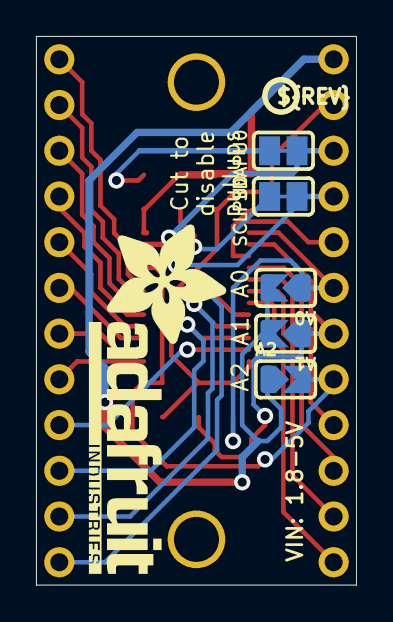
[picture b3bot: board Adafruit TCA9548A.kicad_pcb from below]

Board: 2 copper layers, 17.8 x 30.5 mm, 21 parts (7 on the bottom side), 26 nets.

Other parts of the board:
U$6: PCBFEAT-REV-040
U$7: ADAFRUIT_TEXT_20MM
